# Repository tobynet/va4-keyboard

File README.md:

# The DIY Keyboard `va4` (v0.3.x)

`va4` the 4x2 key split keyboard.

**`OEM Profile Keycaps` + `CherryMX Compatible Switch`** version: (`v0.3.0`)

**`G20 Profile Keycaps` + `CherryMX Compatible Switch`** version: (`v0.2.0`)

**`Kailh Choc(Low profile)` Key Switch** version: (`v0.2.0`)

## Features

* ⌨️ Support `Cherry MX Compatible Switch` and `Kailh Low Profile Choc Switch`

* 🖥️ Support `Pro Micro` compatible board

* 🔑 Password writing space

* 🥚 Columbus' egg included

* 📜 Open Source License

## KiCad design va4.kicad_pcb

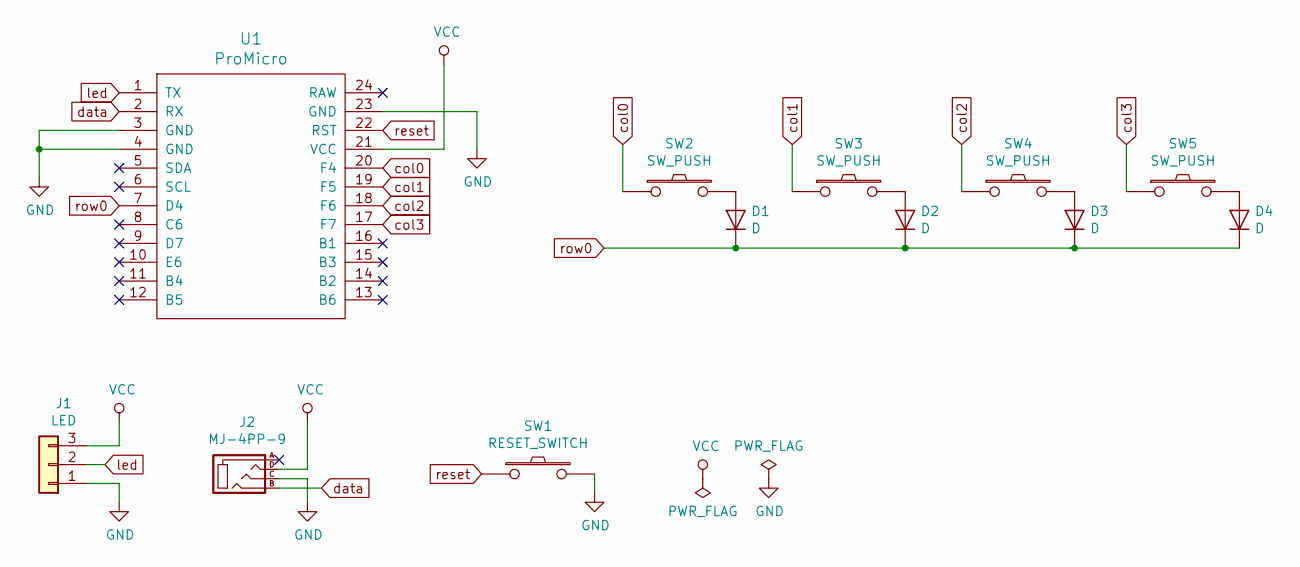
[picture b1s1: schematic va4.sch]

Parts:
D1, D2, D3, D4: D; D3_TH_SMD
J1: LED; StripLED_rev
J2: MJ-4PP-9
SW1: RESET_SWITCH; ResetSW
SW2, SW3, SW4, SW5: SW_PUSH; MX_ALPS_PG1350_noLed
U1: ProMicro; ProMicro_v2

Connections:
GND: J1.1, J2.C, SW1.2, U1.3 (GND), U1.4 (GND), U1.23 (GND)
unnamed: D1.2 (A), SW2.2
unnamed: D2.2 (A), SW3.2
unnamed: D3.2 (A), SW4.2
unnamed: D4.2 (A), SW5.2
VCC: J1.3, J2.D, U1.21 (VCC)
col0: SW2.1, U1.20 (F4)
col1: SW3.1, U1.19 (F5)
col2: SW4.1, U1.18 (F6)
col3: SW5.1, U1.17 (F7)
data: J2.B, U1.2 (RX)
led: J1.2, U1.1 (TX)
reset: SW1.1, U1.22 (RST)
row0: D1.1 (K), D2.1 (K), D3.1 (K), D4.1 (K), U1.7 (D4)

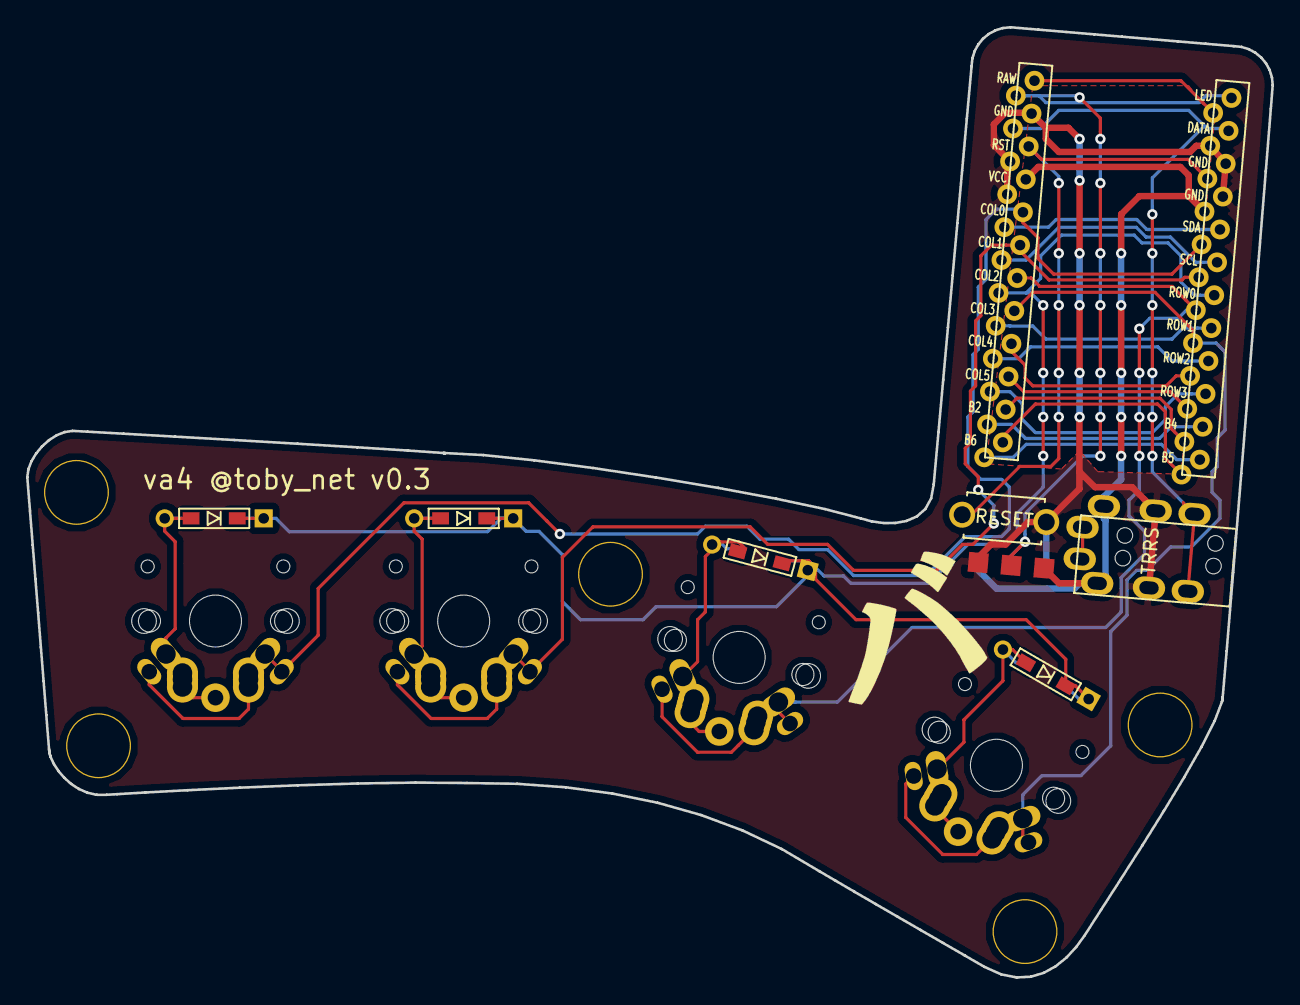
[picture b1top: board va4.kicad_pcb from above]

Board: 2 copper layers, 95.8 x 73.1 mm, 17 parts (0 on the bottom side), 14 nets.

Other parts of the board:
Ref**: Val**; HOLE
Ref**#2, Ref**#3, Ref**#4, Ref**#5: Val**; HOLE

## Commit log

2018-12-03 Use github.com/foostan/kbd
    * MIT License
2018-12-03 Add schematic
2018-12-03 Assign footprints to schematic symbols
2018-12-03 Add pcb
2018-12-04 Add gerber files
2018-12-04 Add data for a plate
2019-01-20 Fix 4th key layout for Kailh Choc key switch(low profile)
2019-01-20 Update gerber files
2019-01-20 Semi-automatic gerber zip generator
2019-01-21 Fix plates for lower connecters and Kailh Choc key switch
2019-01-21 Add README and LICENSE
2019-02-10 Fix version #5
2019-02-10 Add photos of v0.3.0 and replace some of them in README.md
2019-02-10 Add emoji
